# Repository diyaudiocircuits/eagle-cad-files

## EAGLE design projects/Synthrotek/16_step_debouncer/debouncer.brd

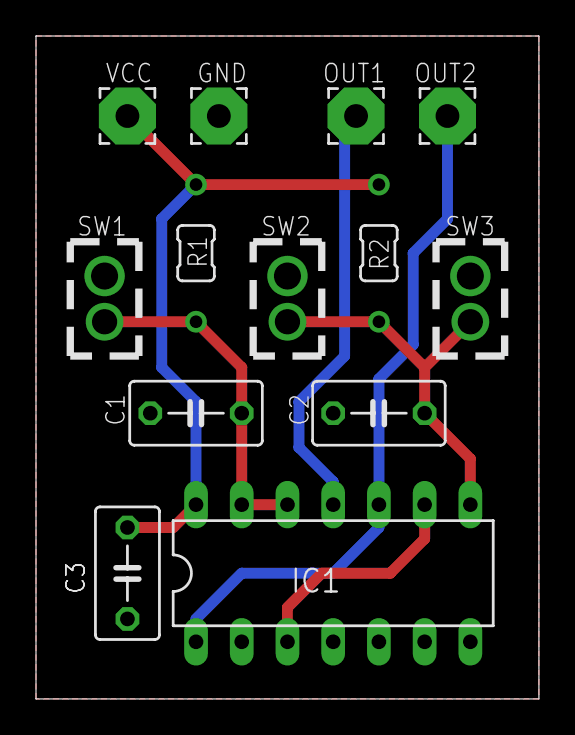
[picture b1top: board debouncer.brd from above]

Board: 2 copper layers, 27.9 x 36.8 mm, 13 parts (0 on the bottom side), 7 nets.

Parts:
C1, C2, C3: CERAMIC_CAPACITOR; CERAMIC_CAP
GND: WIREPAD3,17/1,3; 3,17/1,3
IC1: 4093N; DIL14
PAD1, PAD2: WIREPAD3,17/1,3; 3,17/1,3
R1, R2: 3MM.3; R0204/3
SW1, SW2, SW3: MOMENTARY_SW_SMALL
VCC: WIREPAD3,17/1,3; 3,17/1,3

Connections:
GND: C1.2, C2.2, C3.2, GND.1, IC1.2, IC1.5, IC1.6, IC1.7, SW1.P$1, SW2.P$1, SW3.P$1
unnamed: C2.1, IC1.8, R2.1, SW2.P$2, SW3.P$2
unnamed: IC1.3, IC1.9
unnamed: C1.1, IC1.12, IC1.13, R1.1, SW1.P$2
unnamed: IC1.11, PAD1.1
unnamed: IC1.1, IC1.10, PAD2.1
VCC: C3.1, IC1.14, R1.2, R2.2, VCC.1
